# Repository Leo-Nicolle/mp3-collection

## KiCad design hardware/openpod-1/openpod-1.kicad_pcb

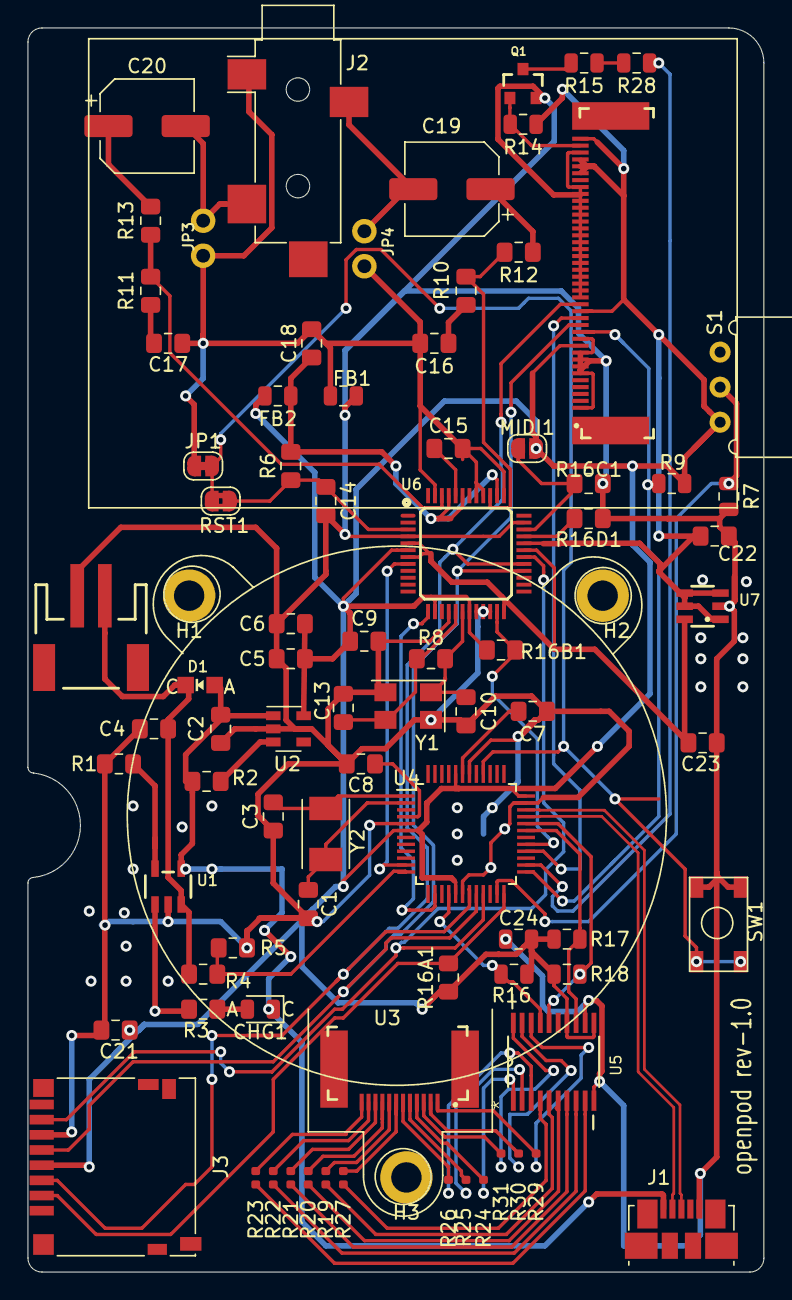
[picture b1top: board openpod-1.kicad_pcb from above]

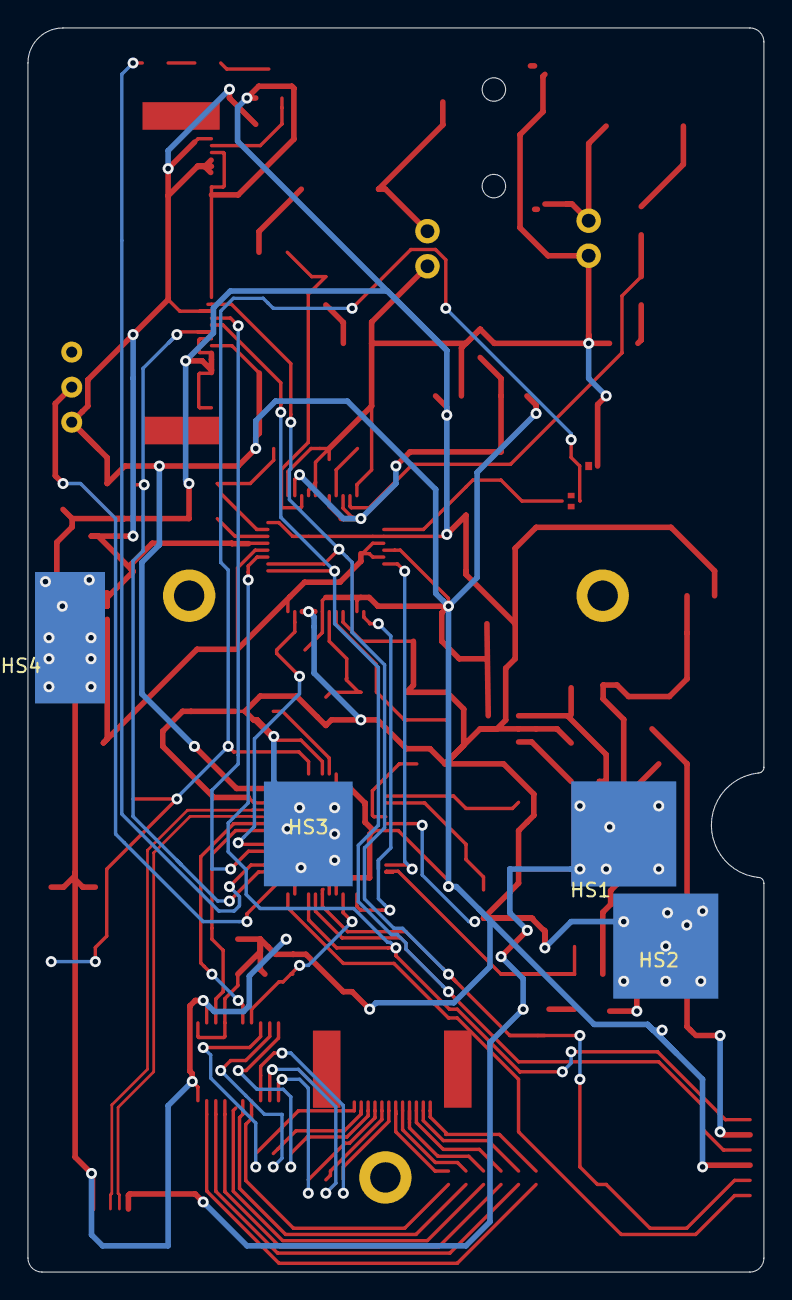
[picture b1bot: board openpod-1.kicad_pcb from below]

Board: 4 copper layers, 53.3 x 90.2 mm, 90 parts (4 on the bottom side), 74 nets.

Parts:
C1, C3, C10, C13: 22pF; C_0805_2012Metric_Pad1.15x1.40mm_HandSolder
C2, C4, C5, C9, C22, C23: 10uF; C_0805_2012Metric_Pad1.15x1.40mm_HandSolder
C6, C7, C8, C15, C18, C21: 1uF; C_0805_2012Metric_Pad1.15x1.40mm_HandSolder
C14: 0.1uF; C_0805_2012Metric_Pad1.15x1.40mm_HandSolder
C16, C17: 10nF; C_0805_2012Metric_Pad1.15x1.40mm_HandSolder
C19, C20: 220uF; CP_Elec_6.3x5.4
C24: 0.1uF; C_0805_2012Metric
CHG1: ORANGE; LED_0805_2012Metric
D1: MBR120; CHIPLED_0805_NOOUTLINE
FB1, FB2: Ferrite_Bead; C_0805_2012Metric
H1, H2, H3: MountingHole; MountingHole_2.2mm_M2_DIN965_Pad
HS1, HS2: Heatsink_Pad; medium-thermal
HS3: Heatsink_Pad; thermal
HS4: Heatsink_Pad; small-thermal
J1: USB_B_Micro; USB_Micro-B_Molex_47346-0001
J2: SJ-3524-SMT-jack; Jack_3.5mm_CUI_SJ-3524-SMT_Horizontal
J3: Micro_SD_Card; microSD_HC_Hirose_DM3D-SF
JP1: SolderJumper_2_Bridged; SolderJumper-2_P1.3mm_Bridged_RoundedPad1.0x1.5mm
JP3, JP4: HEADER-1X2ROUND; 1X02_ROUND
MIDI1: SolderJumper; SolderJumper-2_P1.3mm_Open_RoundedPad1.0x1.5mm
Q1: 220mA/50V/3.5Ω; SOT23-3
R1: 10k; R_0805_2012Metric_Pad1.15x1.40mm_HandSolder
R2, R4, R5, R6, R16A1, R16B1, R16C1, R16D1: 100k; R_0805_2012Metric_Pad1.15x1.40mm_HandSolder
R3: 1k; R_0805_2012Metric_Pad1.15x1.40mm_HandSolder
R7, R9, R14, R17, R18: 10k; R_0805_2012Metric
R8: 1M; R_0805_2012Metric_Pad1.15x1.40mm_HandSolder
R10, R11: 22; R_0805_2012Metric_Pad1.15x1.40mm_HandSolder
R12, R13: 100; R_0805_2012Metric_Pad1.15x1.40mm_HandSolder
R15, R28: 1; R_0805_2012Metric
R16: 47k; R_0805_2012Metric
R19, R20, R21, R22, R23, R24, R25, R26, R27, R29, R30, R31: 1k; R_0402_1005Metric
RST1: SolderJumper_2_Bridged; SolderJumper-2_P1.3mm_Bridged2Bar_RoundedPad1.0x1.5mm
S1: 450302014072; slider
SW1: SW_Push; PTS647
U1: MCP73831-2-OT; SOT23-5
U2: SPX3819M5-L-3-3; SOT-23-5
U3: click-wheel; connector
U4: ATSAMD21G18A-AUT; TQFP-48_7x7mm_P0.5mm
U5: AT42QT2120_COMMS; QT2120
U6: VS1053B; LQFP48
U7: TLV733P-Q1; SOT23-6
U8: KWH018ST14-F01_4WSPI-TOP; FPC05040-17204
X2: JSTPH; JST-2-SMD
Y1: ABM8G-12.288MHZ-18-D2Y-T; Crystal_SMD_5032-4Pin_5.0x3.2mm
Y2: Crystal; Crystal_SMD_TXC_7A-2Pin_5x3.2mm

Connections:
+1V8: C23.1, U6.5, U6.7, U6.24, U6.31, U7.6
+3V3: C5.1, C6.1, C9.1, C21.1, C22.1, C24.1, FB2.2, J3.4, MIDI1.1, R9.1, R14.1, R16.1, R16A1.1, R16B1.1, R17.1, R18.2, S1.2, U2.5, U4.6, U4.17, U4.36, U4.44, U5.11, U5.14, U6.6, U6.14, U6.19, U6.32, U7.1, U7.3, U7.4, U7.5, U8.P$10, U8.P$15, U8.P$35, U8.P$36, U8.P$37, U8.P$40
AGND: C15.2, C16.2, C17.2, C18.2, FB1.1, J2.S, JP1.1, JP3.2, JP4.2, U6.37, U6.40, U6.41, U6.47
AREF: C8.1, U4.4
AVDD: C18.1, FB2.1, R6.2, U6.38, U6.43, U6.45
D0: R16.2, U4.16, U5.17
D2: R7.1, S1.1, U4.23
D3: U4.14, U6.13
D5: J3.2, R16A1.2, U4.24
D6: R16B1.2, U4.29, U6.23
D8: U4.11, U6.8
D9: R4.2, R5.1, U4.12
D11: R9.2, U4.25, U8.P$12
D12: U4.28, U8.P$14
D13: R28.1, U4.26
D+: J1.3, U4.34
D-: J1.2, U4.33
Earth: C1.1, C2.2, C3.1, C4.2, C5.2, C6.2, C7.1, C8.2, C9.2, C10.2, C13.2, C14.2, C21.2, C22.2, C23.2, C24.2, FB1.2, HS2.1, HS3.1, HS4.1, J1.5, J3.6, Q1.2, R1.1, R5.2, R7.2, R16C1.2, R16D1.2, SW1.2, U1.2, U2.2, U4.5, U4.18, U4.35, U4.42, U5.10, U5.12, U6.4, U6.16, U6.20, U6.21, U6.22, U6.35, U7.2, U8.P$1, U8.P$6, U8.P$7, U8.P$8, U8.P$9, U8.P$11, U8.P$17, U8.P$18, U8.P$19, U8.P$20, U8.P$21, U8.P$22, U8.P$23, U8.P$24, U8.P$25, U8.P$26, U8.P$27, U8.P$28, U8.P$29, U8.P$30, U8.P$31, U8.P$32, U8.P$33, U8.P$38, X2.2, Y1.2, Y1.4
GPIO0: R16D1.1, U6.33
GPIO1: MIDI1.2, R16C1.1, U6.34
LEDK: Q1.1, R14.2, U8.P$39
LEFT: R11.1, R13.2, U6.46
L_OUT: C20.2, J2.T, JP3.1
MISO: J3.7, U4.21, U6.30
MOSI: J3.3, U4.19, U6.29, U8.P$16
MP3RST: C14.1, R6.1, RST1.1, U6.3
unnamed: C1.2, U4.2, Y2.1
unnamed: C3.2, U4.1, Y2.2
unnamed: C7.2, U4.43
unnamed: C10.1, R8.1, U6.18, Y1.1
unnamed: C13.1, R8.2, U6.17, Y1.3
unnamed: C15.1, U6.44
unnamed: C16.1, R10.2
unnamed: C17.1, R11.2
unnamed: C19.1, R12.1
unnamed: C20.1, R13.1
unnamed: CHG1.2, R3.1
unnamed: Q1.3, R15.2
unnamed: R1.2, U1.5
unnamed: R2.2, U2.3
unnamed: R3.2, U1.1
unnamed: R15.1, R28.2
unnamed: R19.1, U5.5
unnamed: R19.2, U3.8
unnamed: R20.1, U5.6
unnamed: R20.2, U3.9
unnamed: R21.1, U5.7
unnamed: R21.2, U3.10
unnamed: R22.1, U5.8
unnamed: R22.2, U3.11
unnamed: R23.1, U5.9
unnamed: R23.2, U3.12
unnamed: R24.1, U5.1
unnamed: R24.2, U3.4
unnamed: R25.1, U5.2
unnamed: R25.2, U3.5
unnamed: R26.1, U5.3
unnamed: R26.2, U3.6
unnamed: R27.1, U5.4
unnamed: R27.2, U3.7
unnamed: R29.1, U5.18
unnamed: R29.2, U3.1
unnamed: R30.1, U5.19
unnamed: R30.2, U3.2
unnamed: R31.1, U5.20
unnamed: R31.2, U3.3
RESET: JP1.2, RST1.2, SW1.1, U4.40
RIGHT: R10.1, R12.2, U6.39
R_OUT: C19.2, J2.R, JP4.1
SCK: J3.5, U4.20, U6.28, U8.P$13
SCL: R18.1, U4.32, U5.16
SDA: R17.2, U4.31, U5.13
VBAT: C4.1, D1.C, R4.1, U1.3, X2.1
VBUS: C2.1, CHG1.1, D1.A, HS1.1, J1.1, R2.1, U1.4, U2.1

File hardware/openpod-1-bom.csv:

Reference, Quantity, Value, Footprint, Datasheet, Mouser Number,Manufacturer, Reference,Alt1,Alt1- Manufacturer,Alt2
C1 C3 C13 C10 ,4,22pF,Capacitor_SMD:C_0805_2012Metric_Pad1.15x1.40mm_HandSolder,https://au.mouser.com/datasheet/2/212/KEM_C1062_C0G_FT-CAP_S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,80-C0805X220F5G,KEMET ,C0805X220F5GAC,,,
C14 C24 ,1,0.1uF,Capacitor_SMD:C_0805_2012Metric_Pad1.15x1.40mm_HandSolder,https://au.mouser.com/datasheet/2/212/KEM_C1062_C0G_FT-CAP_S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,80-C0805X104K4R,KEMET ,C0805X104K4RAC ,,,
C16 C17 ,2,10nF,Capacitor_SMD:C_0805_2012Metric_Pad1.15x1.40mm_HandSolder,https://au.mouser.com/datasheet/2/212/KEM_C1062_C0G_FT-CAP_S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,80-C0805X103J3G7800 ,KEMET ,C0805X103J3GACTU ,,,
C19 C20 ,2,220uF,Capacitor_SMD:CP_Elec_6.3x5.4,https://au.mouser.com/datasheet/2/315/ABA0000C1145-947633.pdf,"667-EEE-0JA221WP Panasonic
",KEMET ,EEE-0JA221WP,,,
C4 C5 C2 C9 C22 C23 ,6,10uF,Capacitor_SMD:C_0805_2012Metric_Pad1.15x1.40mm_HandSolder,https://au.mouser.com/datasheet/2/212/KEM_C1062_C0G_FT-CAP_S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,80-C0805C106K9P7210 ,KEMET ,C0805C106K9PAC7210 ,,,
C6 C8 C7 C15 C18 C21 ,6,1uF,Capacitor_SMD:C_0805_2012Metric_Pad1.15x1.40mm_HandSolder,https://au.mouser.com/datasheet/2/212/KEM_C1062_C0G_FT-CAP_S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,80-C0805X105K3R3316,KEMET ,C0805X105K3RAC3316,,,
CHG1 ,1,ORANGE,LED_SMD:LED_0805_2012Metric,~,645-599-0110-007F,Dialight,599-0130-007F,,,
D1 ,1,MBR120,mpr121:CHIPLED_0805_NOOUTLINE,https://au.mouser.com/datasheet/2/308/MBR120VLSFT1-D-107081.pdf,863-MBR120VLSFT3G,ON Semiconductor,MBR120VLSFT3G,MBR120VLSFT3,,
FB2 FB1 ,2,Ferrite_Bead,Capacitor_SMD:C_0805_2012Metric,https://au.mouser.com/datasheet/2/281/QNFA9102-1485076.pdf,BLM21SP181SH1D,Murata Electronics ,BLM21SP181SH1D,74279220181,Wurth Electronik,
H1 H2 H3 ,3,MountingHole,MountingHole:MountingHole_2.2mm_M2_DIN965_Pad,~,,~,~,,,
HS1 HS2 ,2,Heatsink_Pad,custom:medium-thermal,~,,~,~,,,
HS3 ,1,Heatsink_Pad,custom:thermal,~,,~,~,,,
HS4 ,1,Heatsink_Pad,custom:small-thermal,~,,~,~,,,
J1 ,1,USB_B_Micro,Connector_USB:USB_Micro-B_Molex_47346-0001,https://au.mouser.com/datasheet/2/276/0473460001_IO_CONNECTO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,538-47346-0001,Molex ,47346-0001,,,
J2 ,1,SJ-3524-SMT-jack,Connector_Audio:Jack_3.5mm_CUI_SJ-3524-SMT_Horizontal,https://au.mouser.com/datasheet/2/670/sj-352x-smt_series-131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,490-SJ-3523-SMT-TR CUI,,SJ-3523-SMT-TR ,,,
J3 ,1,Micro_SD_Card,Connector_Card:microSD_HC_Hirose_DM3D-SF,https://au.mouser.com/datasheet/2/185/DM3_catalog-939223.pdf,798-DM3D-SF,Hirose Connector,DM3D-SF,,,
JP1 ,1,SolderJumper_2_Bridged,Jumper:SolderJumper-2_P1.3mm_Bridged_RoundedPad1.0x1.5mm,~,~,~,~,,,
JP3 JP4 ,2,HEADER-1X2ROUND,adafruit -music:1X02_ROUND,~,~,~,~,,,
MIDI1 ,1,SolderJumper,Jumper:SolderJumper-2_P1.3mm_Open_RoundedPad1.0x1.5mm,~,~,~,~,,,
Q1 ,1,220mA/50V/3.5Ω,sparkfun:SOT23-3,https://www.mouser.com/ds/2/149/BSS138-1006682.pdf,512-BSS138 ,ON Semiconductor,BSS138 ,BSS138(W)(L)(K),,
R1 R17 R18 R7 R9 R14 ,1,10k,Resistor_SMD:R_0805_2012Metric_Pad1.15x1.40mm_HandSolder,https://au.mouser.com/datasheet/2/427/crcwce3-1223726.pdf,71-CRCW080510K0FKEAC,Vishay,CRCW080510K0FKEAC,,,
R10 R11 ,2,22,Resistor_SMD:R_0805_2012Metric_Pad1.15x1.40mm_HandSolder,https://au.mouser.com/datasheet/2/427/crcwce3-1223726.pdf,71-CRCW080522R0FKEA,Vishay,CRCW080522R0FKEA,,,
R12 R13 ,2,100,Resistor_SMD:R_0805_2012Metric_Pad1.15x1.40mm_HandSolder,https://au.mouser.com/datasheet/2/427/crcwce3-1223726.pdf,71-CRCW0805100RFKEAC,Vishay,CRCW0805100RFKEAC,,,
R15 R28 ,2,1,Resistor_SMD:R_0805_2012Metric,https://au.mouser.com/datasheet/2/427/crcwce3-1223726.pdf,71-CRCW08051R00FKEAC,Vishay,CRCW08051R00FKEAC,,,
R16 ,1,47k,Resistor_SMD:R_0805_2012Metric,https://au.mouser.com/datasheet/2/427/crcwce3-1223726.pdf,71-CRCW080547K0FKEAC ,Vishay,CRCW080547K0FKEAC ,,,
R23 R22 R21 R20 R19 R27 R26 R25 R24 R31 R30 R29 ,12,1k,Resistor_SMD:R_0402_1005Metric,https://au.mouser.com/datasheet/2/427/crcwce3-1223726.pdf,71-CRCW04021K00FKEDC,Vishay,CRCW04021K00FKEDC,,,
R3 ,1,1k,Resistor_SMD:R_0805_2012Metric_Pad1.15x1.40mm_HandSolder,https://au.mouser.com/datasheet/2/427/crcwce3-1223726.pdf,71-CRCW08051K00FKEAC,Vishay,CRCW08051K00FKEAC,,,
R5 R4 R2 R6 R16B1 R16A1 R16C1 R16D1 ,8,100k,Resistor_SMD:R_0805_2012Metric_Pad1.15x1.40mm_HandSolder,https://au.mouser.com/datasheet/2/427/crcwce3-1223726.pdf,71-CRCW0805100KFKEAC,Vishay,CRCW0805100KFKEAC,,,
R8 ,1,1M,Resistor_SMD:R_0805_2012Metric_Pad1.15x1.40mm_HandSolder,https://au.mouser.com/datasheet/2/427/crcwce3-1223726.pdf,71-CRCW08051M00FKEAC,Vishay,CRCW08051M00FKEAC,,,
RST1 ,1,SolderJumper_2_Bridged,Jumper:SolderJumper-2_P1.3mm_Bridged2Bar_RoundedPad1.0x1.5mm,~,~,~,~,,,
S1 ,1,450302014072,slider:slider,https://au.mouser.com/datasheet/2/445/450302014072-1626986.pdf,710-450302014072,Wurth Elektronik ,450302014072,,,
SW1 ,1,SW_Push,reset-button:PTS647,https://www.ckswitches.com/media/2567/pts647.pdf,611-PTS647SM38SMTR2L,C&K ,PTS647SM38SMTR2LFS,,,
U1 ,1,MCP73831-2-OT,adafruit-m0:SOT23-5,https://au.mouser.com/datasheet/2/268/20001984g-846362.pdf,579-MCP73831T-2ACIOT,Microchip Technology ,MCP73831T-2ACI/OT,,,
U2 ,1,SPX3819M5-L-3-3,Package_TO_SOT_SMD:SOT-23-5,https://au.mouser.com/datasheet/2/146/SPX3819-1079947.pdf,701-SPX3819M5-L-50TR,MaxLinear ,SPX3819M5-L-5-0/TR,,,
U3 ,1,click-wheel,click-wheel-2:connector,https://omronfs.omron.com/en_US/ecb/products/pdf/en-xf3m.pdf,653-XF3M-1215-1B,Omron Electronics,XF3M-1215-1B,,,
U4 ,1,ATSAMD21G18A-AUT,Package_QFP:TQFP-48_7x7mm_P0.5mm,http://ww1.microchip.com/downloads/en/DeviceDoc/SAMD21-Famil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,556-ATSAMD21G18A-AUT ,AMTEL,ATSAMD21G18A-AUT,,,
U5 ,1,AT42QT2120_COMMS,little-helper:QT2120,https://au.mouser.com/datasheet/2/268/doc9634-1369146.pdf,556-AT42QT2120-SUR,AMTEL,AT42QT2120-SUR,,,
U6 ,1,VS1053B,adafruit -music:LQFP48,http://www.vlsi.fi/fileadmin/datasheets/vs8053.pdf,485-1681 ,Adafruit ,1681,COM-08892,Sparkfun,
U7 ,1,TLV733P-Q1,adafruit -music:SOT23-6,http://www.ti.com/lit/ds/symlink/tlv733p-q1.pdf?HQS=TI-null-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,595-TLV73318PQDBVRQ1,Texas Instruments ,TLV73318PQDBVRQ1 ,,,
U8 ,1,KWH018ST14-F01_4WSPI-TOP,sparkfun:FPC05040-17204,https://omronfs.omron.com/en_US/ecb/products/pdf/en-xf3m.pdf, 653-XF3M-4015-1B,Omron Electronics,XF3M-4015-1B,,,
X2 ,1,JSTPH,little-helper:JST-2-SMD,http://www.jst-mfg.com/product/pdf/eng/ePH.pdf,~,JST Sales America Inc.,S2B-PH-SM4-TB(LF)(SN) ,,,
Y1 ,1,ABM8G-12.288MHZ-18-D2Y-T,Crystal:Crystal_SMD_5032-4Pin_5.0x3.2mm,https://au.mouser.com/datasheet/2/3/abm3-47699.pdf,815-ABM312288B4YT,ABRACON,ABM3-12.288MHZ-B4Y-T,,,
Y2 ,1,Crystal,Crystal:Crystal_SMD_TXC_7A-2Pin_5x3.2mm,https://au.mouser.com/datasheet/2/3/ABS10-17136.pdf,815-ABS10-32.768K9T,ABRACON,ABS10-32.768KHZ-9-T,,,

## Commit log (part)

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2019-07-22 added nodal choose file
2019-07-22 added store
2019-07-23 save state on server + add some style to the file list
2019-07-23 start generating mp3 files
2019-07-24 cleanner database + save files in database
2019-07-24 added a client-side filter
2019-07-24 put the filters and search in the header
2019-07-24 better hash for files
2019-07-24 better xhr
2019-07-25 start to implement update
2019-07-25 added update function
2019-07-26 more general track list
2019-07-26 added date
2019-07-26 more general getInitialvalue for edit
2019-07-26 added auto tags for artists
2019-07-27 try better database
2019-07-27 fix filters
2019-07-29 better state server
2019-07-31 better tracklist style
2019-08-02 added tooltips
2019-08-02 fix auto update
2019-08-31 update click wheel, use connectors
2019-10-29 Bump eslint-utils from 1.4.0 to 1.4.3 in /client
    Bumps [eslint-utils](https://github.com/mysticatea/eslint-utils) from 1.4.0 to 1.4.3.
    - [Release notes](https://github.com/mysticatea/eslint-utils/releases)
    - [Commits](https://github.com/mysticatea/eslint-utils/compare/v1.4.0...v1.4.3)
2020-04-04 Bump acorn from 6.2.1 to 6.4.1 in /server
    Bumps [acorn](https://github.com/acornjs/acorn) from 6.2.1 to 6.4.1.
    - [Release notes](https://github.com/acornjs/acorn/releases)
    - [Commits](https://github.com/acornjs/acorn/compare/6.2.1...6.4.1)
2020-06-07 Bump websocket-extensions from 0.1.3 to 0.1.4 in /client
    Bumps [websocket-extensions](https://github.com/faye/websocket-extensions-node) from 0.1.3 to 0.1.4.
    - [Release notes](https://github.com/faye/websocket-extensions-node/releases)
    - [Changelog](https://github.com/faye/websocket-extensions-node/blob/master/CHANGELOG.md)
    - [Commits](https://github.com/faye/websocket-extensions-node/compare/0.1.3...0.1.4)
2020-07-17 Bump lodash from 4.17.15 to 4.17.19 in /client
    Bumps [lodash](https://github.com/lodash/lodash) from 4.17.15 to 4.17.19.
    - [Release notes](https://github.com/lodash/lodash/releases)
    - [Commits](https://github.com/lodash/lodash/compare/4.17.15...4.17.19)
2020-07-31 Bump elliptic from 6.5.0 to 6.5.3 in /client
    Bumps [elliptic](https://github.com/indutny/elliptic) from 6.5.0 to 6.5.3.
    - [Release notes](https://github.com/indutny/elliptic/releases)
    - [Commits](https://github.com/indutny/elliptic/compare/v6.5.0...v6.5.3)
2020-09-10 Bump http-proxy from 1.17.0 to 1.18.1 in /client
    Bumps [http-proxy](https://github.com/http-party/node-http-proxy) from 1.17.0 to 1.18.1.
    - [Release notes](https://github.com/http-party/node-http-proxy/releases)
    - [Changelog](https://github.com/http-party/node-http-proxy/blob/master/CHANGELOG.md)
    - [Commits](https://github.com/http-party/node-http-proxy/compare/1.17.0...1.18.1)
2020-11-25 Bump highlight.js from 9.15.8 to 9.18.5 in /client
    Bumps [highlight.js](https://github.com/highlightjs/highlight.js) from 9.15.8 to 9.18.5.
    - [Release notes](https://github.com/highlightjs/highlight.js/releases)
    - [Changelog](https://github.com/highlightjs/highlight.js/blob/9.18.5/CHANGES.md)
    - [Commits](https://github.com/highlightjs/highlight.js/compare/9.15.8...9.18.5)
2021-01-05 Bump axios from 0.19.0 to 0.21.1 in /client
    Bumps [axios](https://github.com/axios/axios) from 0.19.0 to 0.21.1.
    - [Release notes](https://github.com/axios/axios/releases)
    - [Changelog](https://github.com/axios/axios/blob/v0.21.1/CHANGELOG.md)
    - [Commits](https://github.com/axios/axios/compare/v0.19.0...v0.21.1)
2021-03-09 Bump elliptic from 6.5.0 to 6.5.4 in /server
    Bumps [elliptic](https://github.com/indutny/elliptic) from 6.5.0 to 6.5.4.
    - [Release notes](https://github.com/indutny/elliptic/releases)
    - [Commits](https://github.com/indutny/elliptic/compare/v6.5.0...v6.5.4)
2021-03-30 Bump y18n from 4.0.0 to 4.0.1 in /server
    Bumps [y18n](https://github.com/yargs/y18n) from 4.0.0 to 4.0.1.
    - [Release notes](https://github.com/yargs/y18n/releases)
    - [Changelog](https://github.com/yargs/y18n/blob/master/CHANGELOG.md)
    - [Commits](https://github.com/yargs/y18n/commits)
2021-04-30 Bump ssri from 6.0.1 to 6.0.2 in /server
    Bumps [ssri](https://github.com/npm/ssri) from 6.0.1 to 6.0.2.
    - [Release notes](https://github.com/npm/ssri/releases)
    - [Changelog](https://github.com/npm/ssri/blob/v6.0.2/CHANGELOG.md)
    - [Commits](https://github.com/npm/ssri/compare/v6.0.1...v6.0.2)
2021-05-08 Bump handlebars from 4.1.2 to 4.7.7 in /client
    Bumps [handlebars](https://github.com/wycats/handlebars.js) from 4.1.2 to 4.7.7.
    - [Release notes](https://github.com/wycats/handlebars.js/releases)
    - [Changelog](https://github.com/handlebars-lang/handlebars.js/blob/master/release-notes.md)
    - [Commits](https://github.com/wycats/handlebars.js/compare/v4.1.2...v4.7.7)
2021-05-10 Bump lodash from 4.17.15 to 4.17.21 in /server
    Bumps [lodash](https://github.com/lodash/lodash) from 4.17.15 to 4.17.21.
    - [Release notes](https://github.com/lodash/lodash/releases)
    - [Commits](https://github.com/lodash/lodash/compare/4.17.15...4.17.21)
2021-05-10 Bump lodash from 4.17.15 to 4.17.21 in /client
    Bumps [lodash](https://github.com/lodash/lodash) from 4.17.15 to 4.17.21.
    - [Release notes](https://github.com/lodash/lodash/releases)
    - [Commits](https://github.com/lodash/lodash/compare/4.17.15...4.17.21)
2021-05-25 Bump browserslist from 4.6.6 to 4.16.6 in /client
    Bumps [browserslist](https://github.com/browserslist/browserslist) from 4.6.6 to 4.16.6.
    - [Release notes](https://github.com/browserslist/browserslist/releases)
    - [Changelog](https://github.com/browserslist/browserslist/blob/main/CHANGELOG.md)
    - [Commits](https://github.com/browserslist/browserslist/compare/4.6.6...4.16.6)
2021-07-01 Bump socket.io-parser from 3.3.0 to 3.3.2 in /server
    Bumps [socket.io-parser](https://github.com/socketio/socket.io-parser) from 3.3.0 to 3.3.2.
    - [Release notes](https://github.com/socketio/socket.io-parser/releases)
    - [Changelog](https://github.com/socketio/socket.io-parser/blob/3.3.2/CHANGELOG.md)
    - [Commits](https://github.com/socketio/socket.io-parser/compare/3.3.0...3.3.2)
    ---
    updated-dependencies:
2021-08-11 Bump path-parse from 1.0.6 to 1.0.7 in /server
    Bumps [path-parse](https://github.com/jbgutierrez/path-parse) from 1.0.6 to 1.0.7.
    - [Release notes](https://github.com/jbgutierrez/path-parse/releases)
    - [Commits](https://github.com/jbgutierrez/path-parse/commits/v1.0.7)
    ---
    updated-dependencies:
    - dependency-name: path-parse
2021-10-06 Bump url-parse from 1.4.7 to 1.5.3 in /client
    Bumps [url-parse](https://github.com/unshiftio/url-parse) from 1.4.7 to 1.5.3.
    - [Release notes](https://github.com/unshiftio/url-parse/releases)
    - [Commits](https://github.com/unshiftio/url-parse/compare/1.4.7...1.5.3)
    ---
    updated-dependencies:
    - dependency-name: url-parse
2022-02-12 Bump ajv from 6.10.2 to 6.12.6 in /server
    Bumps [ajv](https://github.com/ajv-validator/ajv) from 6.10.2 to 6.12.6.
    - [Release notes](https://github.com/ajv-validator/ajv/releases)
    - [Commits](https://github.com/ajv-validator/ajv/compare/v6.10.2...v6.12.6)
    ---
    updated-dependencies:
    - dependency-name: ajv
2022-02-26 Bump url-parse from 1.4.7 to 1.5.10 in /client
    Bumps [url-parse](https://github.com/unshiftio/url-parse) from 1.4.7 to 1.5.10.
    - [Release notes](https://github.com/unshiftio/url-parse/releases)
    - [Commits](https://github.com/unshiftio/url-parse/compare/1.4.7...1.5.10)
    ---
    updated-dependencies:
    - dependency-name: url-parse
2022-06-22 Bump shell-quote from 1.6.1 to 1.7.3 in /client
    Bumps [shell-quote](https://github.com/substack/node-shell-quote) from 1.6.1 to 1.7.3.
    - [Release notes](https://github.com/substack/node-shell-quote/releases)
    - [Changelog](https://github.com/substack/node-shell-quote/blob/master/CHANGELOG.md)
    - [Commits](https://github.com/substack/node-shell-quote/compare/1.6.1...1.7.3)
    ---
    updated-dependencies:
2022-07-20 Bump terser from 4.1.2 to 4.8.1 in /server
    Bumps [terser](https://github.com/terser/terser) from 4.1.2 to 4.8.1.
    - [Release notes](https://github.com/terser/terser/releases)
    - [Changelog](https://github.com/terser/terser/blob/master/CHANGELOG.md)
    - [Commits](https://github.com/terser/terser/commits)
    ---
    updated-dependencies:
2022-09-29 Bump @hapi/hoek and @hapi/joi in /client
    Bumps [@hapi/hoek](https://github.com/hapijs/hoek) and [@hapi/joi](https://github.com/hapijs/joi). These dependencies needed to be updated together.
    Updates `@hapi/hoek` from 6.2.4 to 8.5.1
    - [Release notes](https://github.com/hapijs/hoek/releases)
    - [Commits](https://github.com/hapijs/hoek/compare/v6.2.4...v8.5.1)
    Updates `@hapi/joi` from 15.1.0 to 15.1.1
    - [Release notes](https://github.com/hapijs/joi/releases)
2022-11-12 Bump socket.io-parser from 3.3.0 to 3.3.3 in /client
    Bumps [socket.io-parser](https://github.com/socketio/socket.io-parser) from 3.3.0 to 3.3.3.
    - [Release notes](https://github.com/socketio/socket.io-parser/releases)
    - [Changelog](https://github.com/socketio/socket.io-parser/blob/main/CHANGELOG.md)
    - [Commits](https://github.com/socketio/socket.io-parser/compare/3.3.0...3.3.3)
    ---
    updated-dependencies:
2022-11-18 Bump loader-utils and @vue/cli-service in /client
    Bumps [loader-utils](https://github.com/webpack/loader-utils) to 1.4.2 and updates ancestor dependency [@vue/cli-service](https://github.com/vuejs/vue-cli/tree/HEAD/packages/@vue/cli-service). These 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
    Updates `loader-utils` from 1.2.3 to 1.4.2
    - [Release notes](https://github.com/webpack/loader-utils/releases)
    - [Changelog](https://github.com/webpack/loader-utils/blob/v1.4.2/CHANGELOG.md)
    - [Commits](https://github.com/webpack/loader-utils/compare/v1.2.3...v1.4.2)
    Updates `@vue/cli-service` from 3.9.3 to 5.0.8
2022-11-23 Bump engine.io and socket.io in /server
    Bumps [engine.io](https://github.com/socketio/engine.io) to 3.6.1 and updates ancestor dependency [socket.io](https://github.com/socketio/socket.io). These dependencies need to be updated together.
    Updates `engine.io` from 3.3.2 to 3.6.1
    - [Release notes](https://github.com/socketio/engine.io/releases)
    - [Changelog](https://github.com/socketio/engine.io/blob/main/CHANGELOG.md)
    - [Commits](https://github.com/socketio/engine.io/compare/3.3.2...3.6.1)
    Updates `socket.io` from 2.2.0 to 2.5.0
2022-12-04 Bump decode-uri-component from 0.2.0 to 0.2.2 in /client
    Bumps [decode-uri-component](https://github.com/SamVerschueren/decode-uri-component) from 0.2.0 to 0.2.2.
    - [Release notes](https://github.com/SamVerschueren/decode-uri-component/releases)
    - [Commits](https://github.com/SamVerschueren/decode-uri-component/compare/v0.2.0...v0.2.2)
    ---
    updated-dependencies:
    - dependency-name: decode-uri-component
2022-12-09 Bump qs from 6.5.2 to 6.5.3 in /client
    Bumps [qs](https://github.com/ljharb/qs) from 6.5.2 to 6.5.3.
    - [Release notes](https://github.com/ljharb/qs/releases)
    - [Changelog](https://github.com/ljharb/qs/blob/main/CHANGELOG.md)
    - [Commits](https://github.com/ljharb/qs/compare/v6.5.2...v6.5.3)
    ---
    updated-dependencies:
2022-12-10 Bump express from 4.17.1 to 4.18.2 in /client
    Bumps [express](https://github.com/expressjs/express) from 4.17.1 to 4.18.2.
    - [Release notes](https://github.com/expressjs/express/releases)
    - [Changelog](https://github.com/expressjs/express/blob/master/History.md)
    - [Commits](https://github.com/expressjs/express/compare/4.17.1...4.18.2)
    ---
    updated-dependencies:
